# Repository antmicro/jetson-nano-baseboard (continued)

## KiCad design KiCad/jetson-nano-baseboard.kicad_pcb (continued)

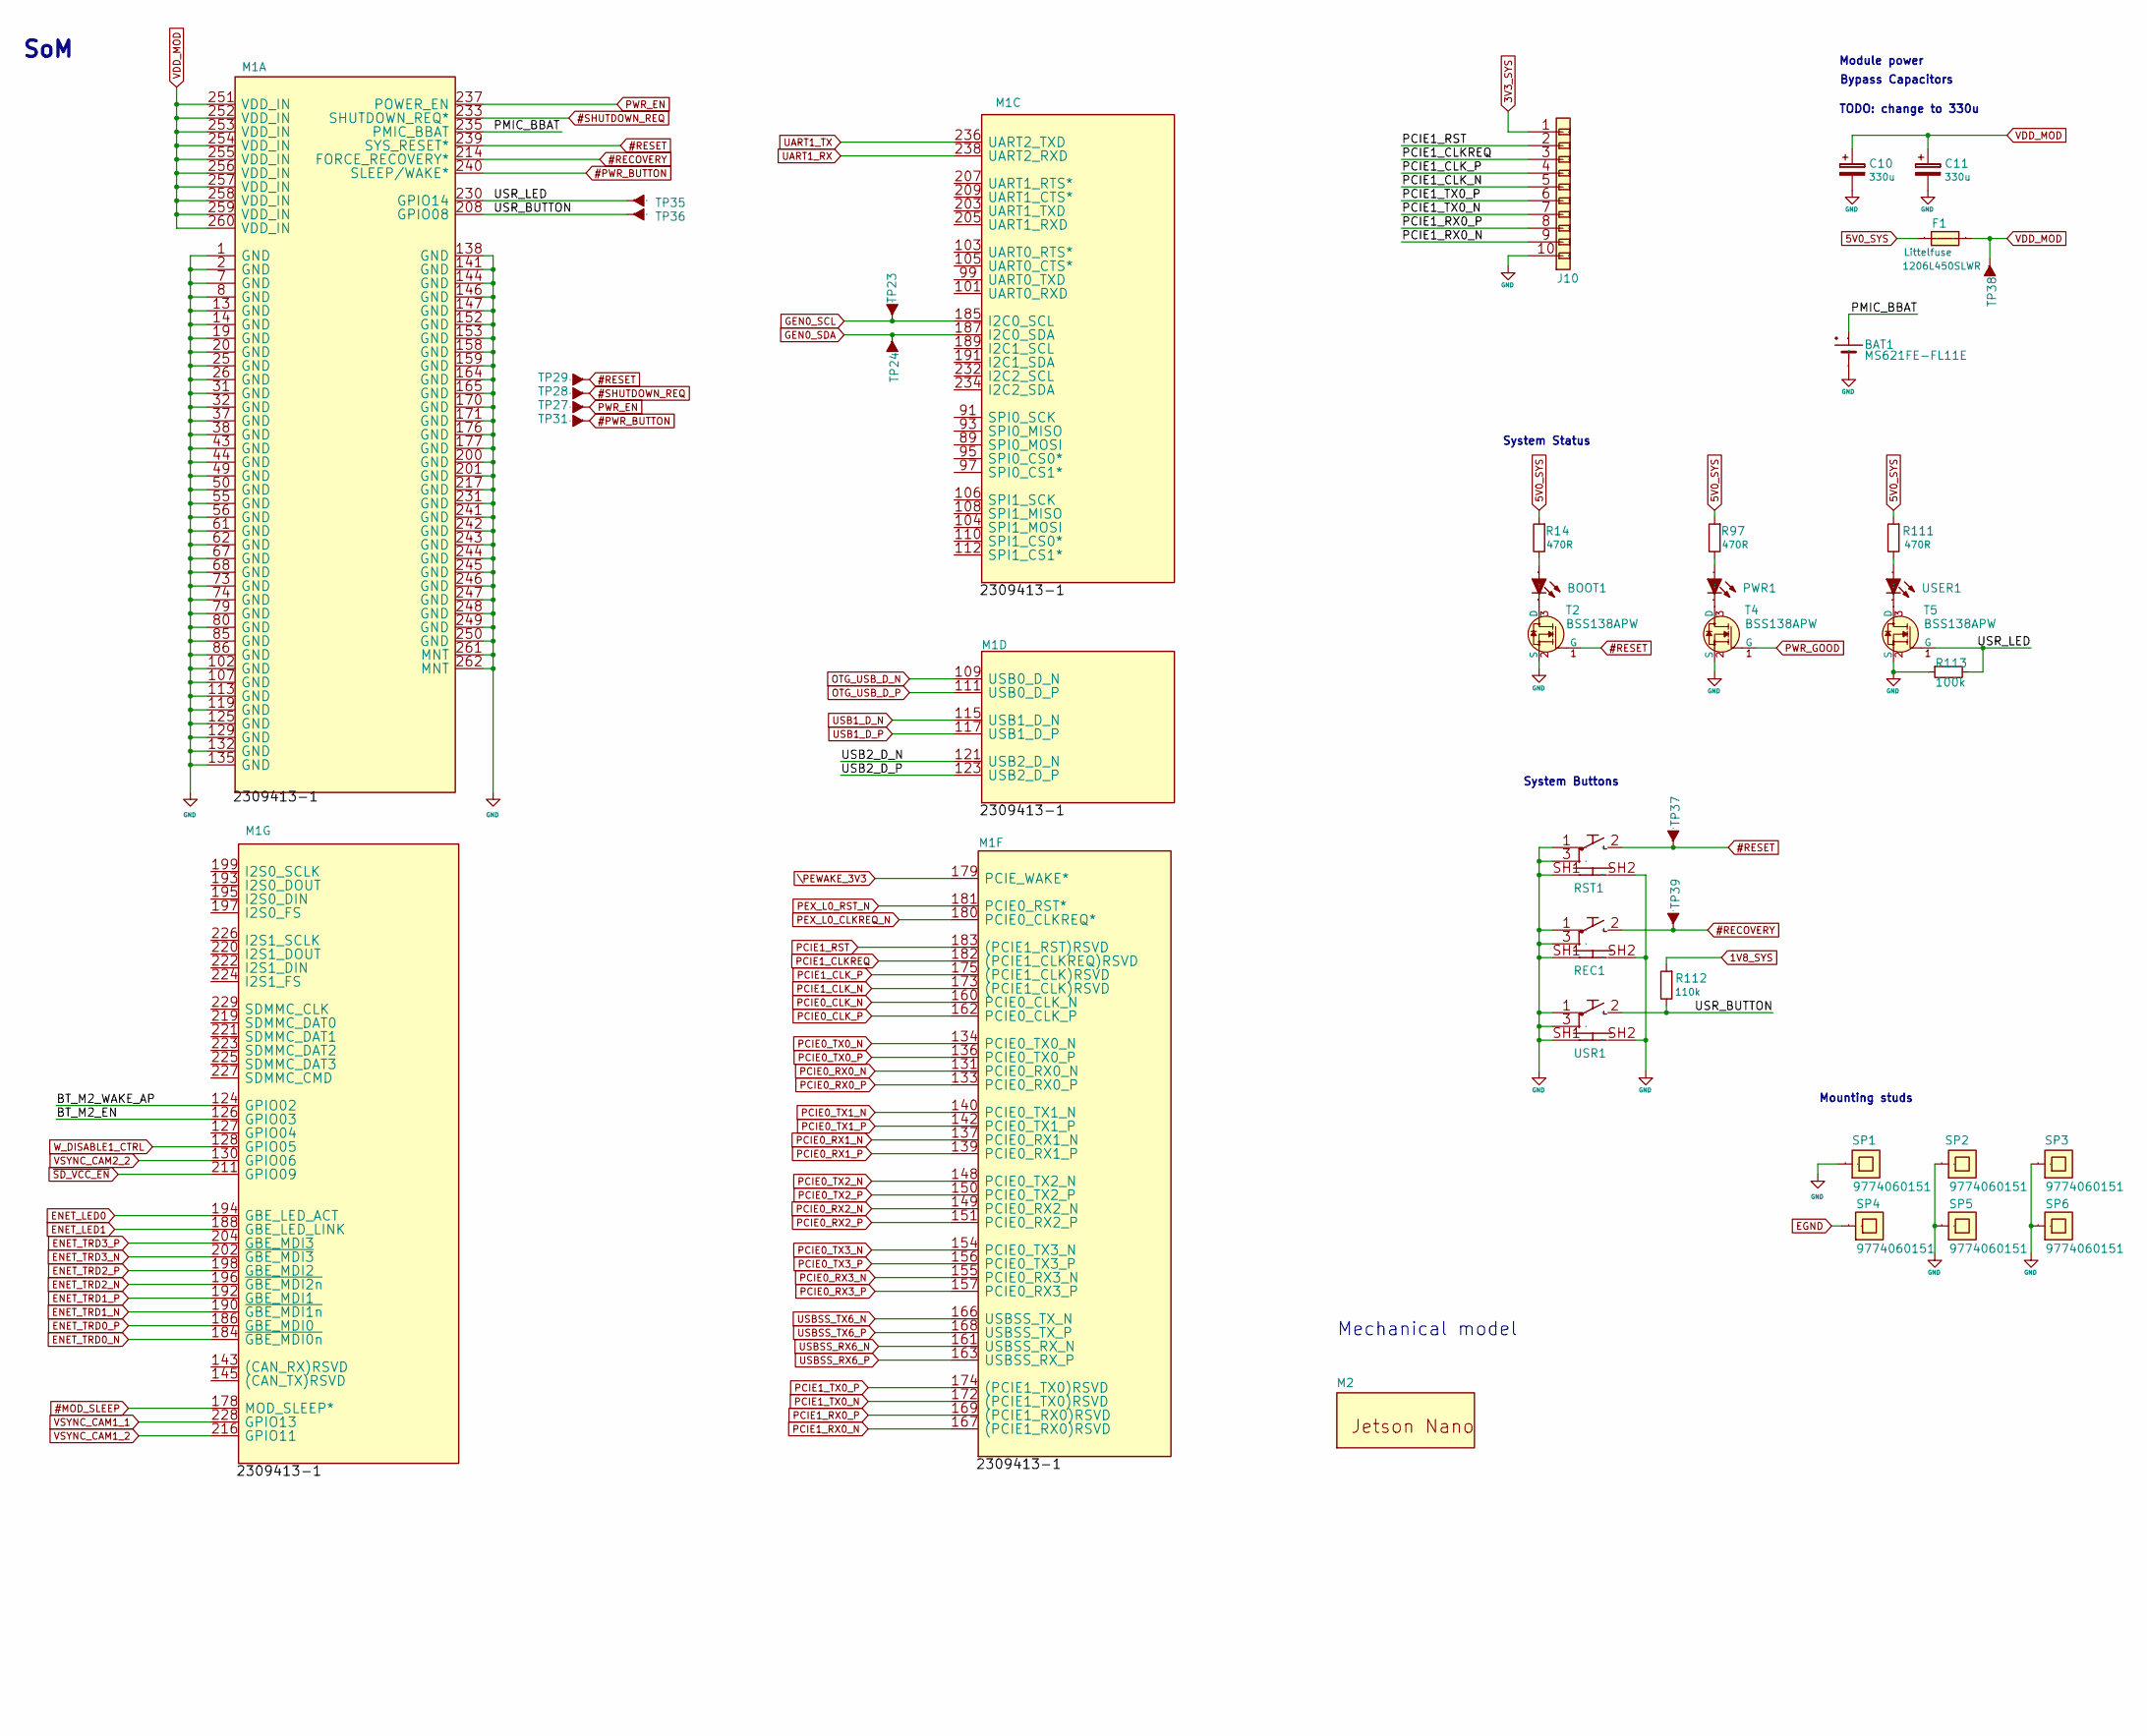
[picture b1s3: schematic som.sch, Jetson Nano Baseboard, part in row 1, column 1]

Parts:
BAT1: MS621FE-FL11E; MPN MS621FE-FL11E
BOOT1: LED0603; MPN KPT-1608SGC
C10, C11: C_330u_KEMET_B; KEMET_B; MPN T520B337M006ATE040
F1: Fuse-1206; PartSymbol 1206L450SLWR
J10: PCA-10; MPN PCA-10
M1, M1_4: jetson-nano-connector; PartSymbol 2309413-1
M2: jetson-nano-module; MPN 900-13448-0020-000
PWR1: LED0603; MPN KPT-1608SGC
R14, R97, R111: R_470R_0402; 0402-res; MPN CRCW0402470RFKED
R112: R_110k_0603; 0603-res; MPN CPF0603B110KE1
R113: 100k; 0402; MPN ERJ2GE0R00X
REC1: TL3340AF160QG; PartSymbol TL3340AF160QG
RST1: TL3340AF160QG; PartSymbol TL3340AF160QG
SP1, SP2, SP3, SP4, SP5, SP6: 9774060151; M2.5-6mm; MPN 9774060151
T2, T4, T5: BSS138APW; SC70-3; MPN BSS138PW
TP23, TP24, TP27, TP28, TP29, TP31, TP35, TP36, TP37, TP38, TP39: TP-R-1.5; MPN N/A
USER1: LED0603; MPN KPT-1608SGC
USR1: TL3340AF160QG; PartSymbol TL3340AF160QG

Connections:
1V8_SYS: R112.2; also elsewhere on the board
3V3_SYS: J10.1; also elsewhere on the board
5V0_SYS: F1.1, R14.2, R97.2, R111.2; also elsewhere on the board
#MOD_SLEEP: M1.178 (MOD_SLEEP*); also elsewhere on the board
#PWR_BUTTON: M1.240 (SLEEP/WAKE*), TP31.1
#RECOVERY: M1.214 (FORCE_RECOVERY*), REC1.2, TP39.1
#RESET: M1.239 (SYS_RESET*), RST1.2, T2.1 (G), TP29.1, TP37.1; also elsewhere on the board
#SHUTDOWN_REQ: M1.233 (SHUTDOWN_REQ*), TP28.1; also elsewhere on the board
/SoM/BT_M2_EN: M1.126 (GPIO03)
/SoM/BT_M2_WAKE_AP: M1.124 (GPIO02)
/SoM/PMIC_BBAT: BAT1.+, M1.235 (PMIC_BBAT)
/SoM/USB2_D_N: M1.121 (USB2_D_N)
/SoM/USB2_D_P: M1.123 (USB2_D_P)
/SoM/USR_BUTTON: M1.208 (GPIO08), R112.1, TP36.1, USR1.2
/SoM/USR_LED: M1.230 (GPIO14), R113.1, T5.1 (G), TP35.1
EGND: SP4.1; also elsewhere on the board
ENET_LED0: M1.194 (GBE_LED_ACT); also elsewhere on the board
ENET_LED1: M1.188 (GBE_LED_LINK); also elsewhere on the board
ENET_TRD0_N: M1.184 (~GBE_MDI0n); also elsewhere on the board
ENET_TRD0_P: M1.186 (GBE_MDI0); also elsewhere on the board
ENET_TRD1_N: M1.190 (~GBE_MDI1n); also elsewhere on the board
ENET_TRD1_P: M1.192 (GBE_MDI1); also elsewhere on the board
ENET_TRD2_N: M1.196 (~GBE_MDI2n); also elsewhere on the board
ENET_TRD2_P: M1.198 (GBE_MDI2); also elsewhere on the board
ENET_TRD3_N: M1.202 (~GBE_MDI3); also elsewhere on the board
ENET_TRD3_P: M1.204 (GBE_MDI3); also elsewhere on the board
GEN0_SCL: M1.185 (I2C0_SCL), TP23.1; also elsewhere on the board
GEN0_SDA: M1.187 (I2C0_SDA), TP24.1; also elsewhere on the board
unnamed: BOOT1.A, R14.1
unnamed: BOOT1.K, T2.3 (D)
unnamed: PWR1.A, R97.1
unnamed: PWR1.K, T4.3 (D)
unnamed: R111.1, USER1.A
unnamed: T5.3 (D), USER1.K
OTG_USB_D_N: M1.109 (USB0_D_N); also elsewhere on the board
OTG_USB_D_P: M1.111 (USB0_D_P); also elsewhere on the board
PCIE0_CLK_N: M1.160 (PCIE0_CLK_N); also elsewhere on the board
PCIE0_CLK_P: M1.162 (PCIE0_CLK_P); also elsewhere on the board
PCIE0_RX0_N: M1.131 (PCIE0_RX0_N); also elsewhere on the board
PCIE0_RX0_P: M1.133 (PCIE0_RX0_P); also elsewhere on the board
PCIE0_RX1_N: M1.137 (PCIE0_RX1_N); also elsewhere on the board
PCIE0_RX1_P: M1.139 (PCIE0_RX1_P); also elsewhere on the board
PCIE0_RX2_N: M1.149 (PCIE0_RX2_N); also elsewhere on the board
PCIE0_RX2_P: M1.151 (PCIE0_RX2_P); also elsewhere on the board
PCIE0_RX3_N: M1.155 (PCIE0_RX3_N); also elsewhere on the board
PCIE0_RX3_P: M1.157 (PCIE0_RX3_P); also elsewhere on the board
PCIE0_TX0_N: M1.134 (PCIE0_TX0_N); also elsewhere on the board
PCIE0_TX0_P: M1.136 (PCIE0_TX0_P); also elsewhere on the board
PCIE0_TX1_N: M1.140 (PCIE0_TX1_N); also elsewhere on the board
PCIE0_TX1_P: M1.142 (PCIE0_TX1_P); also elsewhere on the board
PCIE0_TX2_N: M1.148 (PCIE0_TX2_N); also elsewhere on the board
PCIE0_TX2_P: M1.150 (PCIE0_TX2_P); also elsewhere on the board
PCIE0_TX3_N: M1.154 (PCIE0_TX3_N); also elsewhere on the board
PCIE0_TX3_P: M1.156 (PCIE0_TX3_P); also elsewhere on the board
PCIE1_CLKREQ: J10.3, M1.182 ((PCIE1_CLKREQ)RSVD)
PCIE1_CLK_N: J10.5, M1.173 ((PCIE1_CLK)RSVD)
PCIE1_CLK_P: J10.4, M1.175 ((PCIE1_CLK)RSVD)
PCIE1_RST: J10.2, M1.183 ((PCIE1_RST)RSVD)
PCIE1_RX0_N: J10.9, M1.167 ((PCIE1_RX0)RSVD)
PCIE1_RX0_P: J10.8, M1.169 ((PCIE1_RX0)RSVD)
PCIE1_TX0_N: J10.7, M1.172 ((PCIE1_TX0)RSVD)
PCIE1_TX0_P: J10.6, M1.174 ((PCIE1_TX0)RSVD)
PEX_L0_CLKREQ_N: M1.180 (PCIE0_CLKREQ*); also elsewhere on the board
PEX_L0_RST_N: M1.181 (PCIE0_RST*); also elsewhere on the board
PWR_EN: M1.237 (POWER_EN), TP27.1; also elsewhere on the board
PWR_GOOD: T4.1 (G); also elsewhere on the board
UART1_RX: M1.238 (UART2_RXD); also elsewhere on the board
UART1_TX: M1.236 (UART2_TXD); also elsewhere on the board
USB1_D_N: M1.115 (USB1_D_N); also elsewhere on the board
USB1_D_P: M1.117 (USB1_D_P); also elsewhere on the board
USBSS_RX6_N: M1.161 (USBSS_RX_N); also elsewhere on the board
USBSS_RX6_P: M1.163 (USBSS_RX_P); also elsewhere on the board
USBSS_TX6_N: M1.166 (USBSS_TX_N); also elsewhere on the board
USBSS_TX6_P: M1.168 (USBSS_TX_P); also elsewhere on the board
VDD_MOD: C10.1, C11.1, F1.2, M1.251 (VDD_IN), M1.252 (VDD_IN), M1.253 (VDD_IN), M1.254 (VDD_IN), M1.255 (VDD_IN), M1.256 (VDD_IN), M1.257 (VDD_IN), M1.258 (VDD_IN), M1.259 (VDD_IN), M1.260 (VDD_IN), TP38.1
VSYNC_CAM1_1: M1.228 (GPIO13); also elsewhere on the board
VSYNC_CAM1_2: M1.216 (GPIO11); also elsewhere on the board
VSYNC_CAM2_2: M1.130 (GPIO06); also elsewhere on the board
W_DISABLE1_CTRL: M1.128 (GPIO05)
\PEWAKE_3V3: M1.179 (PCIE_WAKE*); also elsewhere on the board
~SD_VCC_EN~: M1.211 (GPIO09)

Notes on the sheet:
Mechanical model
Mounting studs
Bypass Capacitors
System Buttons
System Status
Module power
Text
SoM
TODO: change to 330u

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
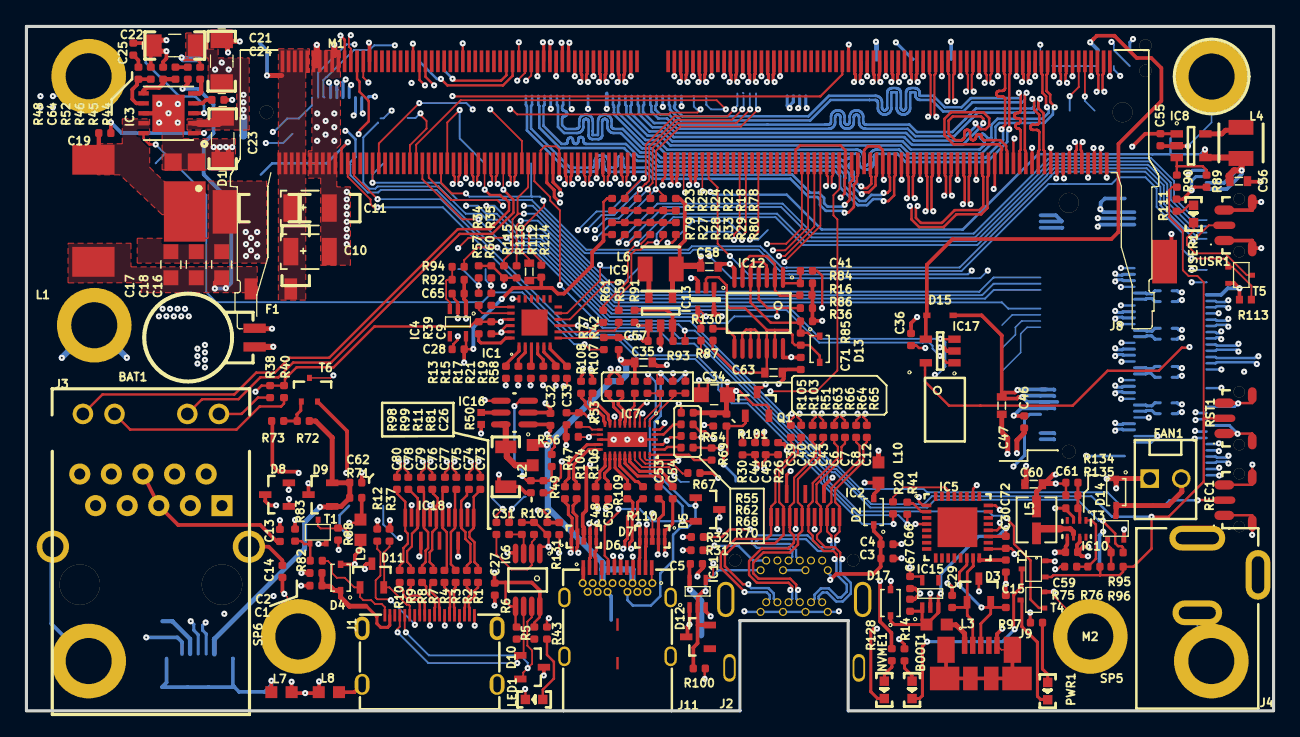
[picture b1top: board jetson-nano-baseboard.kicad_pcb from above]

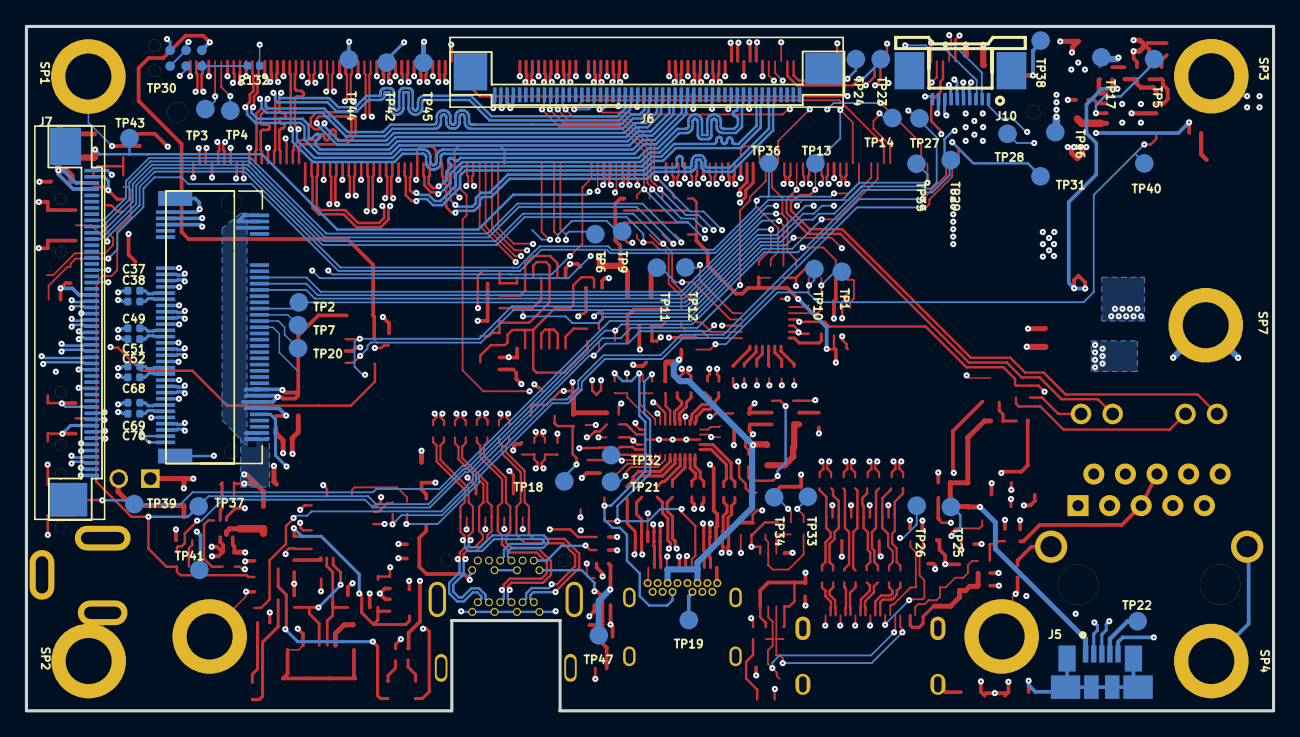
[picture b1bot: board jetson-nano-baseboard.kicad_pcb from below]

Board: 8 copper layers, 100.2 x 55.0 mm, 325 parts (63 on the bottom side), 312 nets.

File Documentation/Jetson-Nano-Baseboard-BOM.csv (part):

Designator,Value,Description,Quantity,PartNumber,Manufacturer,PartSymbol

"BOOT, LED1, PWR","KPT-1608SGC","LED Green 0603 case","3","LED_G","KINGBRIGHT","KPT-1608SGC"
"C1, C2, C3, C4","4u7","MLCC SMT Capacitor 4.7uF 0402","4","C_4u7_0402","MURATA","GRM155R60G475ME"
"C5, C19, C26, C27, C30, C33","100n","MLCC SMT Capacitor 100nF 0603","6","C_100n_0603","AVX","0603YC104KAZ2A"
"C6, C7, C8, C9, C12, C39, C40, C42, C43, C44, C45, C48, C50, C53, C54, C73, C74, C75, C76, C77, C78, C79, C80","100n","MLCC SMT Capacitor 100n 0402","23","C_100n_0402","TDK","C1005X5R0J104K050BA"
"C10, C11","100u","MLCC SMT Capacitor 100uF 1206","2","C_100u_1206","VISHAY","TMCMA0J107MTRF"
"C13","10n","MLCC SMT Capacitor 10 nF 0603","1","C_10n_0603","AVX","06031C103JAT2A"
"C14","100p","MLCC SMT Capacitor 100pF 0603","1","C_100p_0603","Walsin","0603N101J500CT"
"C15, C29","47p","MLCC SMT Capacitor 47pF 0603","2","C_47p_0603","AVX","06031A470KAT2A"
"C16, C17, C18, C34","47u","MLCC SMT Capacitor 47uF 0805","4","C_47u_0805","KEMET","C0805C476M9PACTU"
"C21, C22, C23","2u2","MLCC SMT Capacitor 2.2uF 1206","3","C_2u2_1206","KEMET","C1206C225J5RACTU"
"C24, C61","10n","MLCC SMT Capacitor 10 nF 0402","2","C_10n_0402","AVX","04025G103ZAT2A"
"C25","4n7","MLCC SMT Capacitor 4.7 nF 0402","1","C_4n7_0402","TDK","CGA2B3X7S2A472K050BB"
"C28, C63, C66","1u","MLCC SMT Capacitor 1uF 0402","3","C_1u_0402","MULTICOMP","MC0402F105Z6R3CT"
"C31","100u","MLCC SMT Capacitor 100uF 1210","1","C_100u_1210","SAMSUNG","CL32A107MQVNNNE"
"C32, C59","1u","MLCC SMT Capacitor 1uF 0603","2","C_1u_0603","KEMET","C0603C105M4PACTU"
"C35, C56, C58","10u","MLCC SMT Capacitor 10uF 0603","3","C_10u_0603","Walsin","0603X106M6R3CT"
"C41","47n","MLCC SMT Capacitor 47nF 0402","1","C_47n_0402","MULTICOMP","MC0402X473K160CT"
"C55, C57, C62","4u7","MLCC SMT Capacitor 4.7uF 0603","3","C_4u7_0603","MULTICOMP","MC0603X475K6R3CT"
"C60","10u","MLCC SMT Capacitor 10uF 0402","1","C_10u_0402","TDK","C1005X5R0J106M050BC"
"C64","47p","MLCC SMT Capacitor 47pF 0402","1","C_47p_0402","KEMET","C0402C470J5GACTU"
"C65, C67","2u2","MLCC SMT Capacitor 2.2uF 0402","2","C_2u2_0402","TDK","C1005X5R1A225K050BC"
"D1","PDS760-13","DIODE SCHOTTKY 60V 7A POWERDI5","1","PDS760-13","DIODES INC.","PDS760-13"
"D2, D4, D13, D14","1N4148WS","Diode small signal","4","1N4148WS","ON SEMICONDUCTOR","1N4148WS"
"D3, D5, D8, D9, D10, D11, D12","TPD2E009DRTR","ESD Suppressors 2-CH","7","TPD2E009DRTR","Texas Instruments","TPD2E009DRTR"
"D6, D7","TPD4E05U06","ESD Suppressors 4-CH","2","TPD4E05U06_PASS","Texas Instruments","TPD4E05U06DQAR"
"F1","1206L450SLWR","PTC RESET 6V LO RHO 1206 4.50A","1","LITTELFUSE_1206L450SLWR","LITTELFUSE","1206L450SLWR"
"FAN","MX-22-23-2021","Pinhead connector with key","1","molex_2223-2021","Molex","022232021 A-6373-02A222"
"IC1","TCA9548ARGER","TCA9548ARGER  I2C SWITCH W/ RESET, 8-CH, VQFN-24","1","TCA9548ARGER","Texas Instruments","TCA9548ARGER"
"IC2, IC18","TPD8S009","8-Channel ESD Protection for DisplayPort and HDMI","2","TPD8S009","Texas Instruments","TPD8S009DSMR"
"IC3","TPS54561-Q1","IC REG BCK SPLIT RAIL ADJ 10WSON","1","TPS54561-Q1","Texas Instruments","TPS54561-Q1"
"IC4, IC15","TLV70018DCKT","Voltage Regulator, 2V to 5.5V, 175mV Dropout, 1.8Vout, 200mAout","2","TLV70018DCKT","Texas Instruments","TLV70018DCKT"
"IC5","FT232RQ","USB to serial UART interface","1","FT232RQ","FTDI","FT232RQ-REEL"
"IC6","PCA9517ATP","I2C BUS REPEATER W/ LEVEL TRANS, HWSON-8","1","PCA9517ATP","NXP","PCA9517ATP"
"IC7","HD3SS3220","IC DRP PORT CTLR USB-C 30WQFN","1","HD3SS3220","Texas Instruments","HD3SS3220RNHT"
"IC8, IC9","LM3671MF-3.3","DC/DC Buck Converter","2","LM3671MF-3.3","Texas Instruments","LM3671MF-3.3/NOPB"
"IC10","LP2985-33DBVR","Fixed LDO Voltage Regulator, 2.2V to 16V, 280mV Dropout, 3.3Vout, 150mAout, SOT-23-5","1","LP2985-33DBVR","Texas Instruments","LP2985-33DBVR"
"IC11","SN74LV1T125DCKR","Buffer, 74LV1T125, 1.6 V to 5.5 V, SOT-23-5","1","SN74LV1T125DCKR","Texas Instruments","SN74LV1T125DCKR"
"IC12","74HC00BQ","2 NAND Gate, 4 channel","1","74HC00BQ","NEXPERIA","74HC00BQ"
"IC13","SN74LVC1G126DCKR","Buffer, tri-state","1","SN74LVC1G126DCKR","Texas Instruments","SN74LVC1G126DCKR"
"IC14","SN74LVC1G07DCKR","Buffer, open drain","1","SN74LVC1G07DCKR","Texas Instruments","SN74LVC1G07GW"
"IC16","NCP380HSNAJAAT1G","POWER LOAD SWITCH, HIGH SIDE","1","NCP380HSNAJAAT1G","ON SEMICONDUCTOR","NCP380HSNAJAAT1G"
"J1","685119136923","CONN HDMI FEMALE R/A 19POS 2.6MM","1","WE_685119136923","WURTH ELEKTRONIK","WE_685119136923"
"J2","2129320-3","Mini Displayport Reverse Offset","1","2129320-3","TE Connectivity","2129320-3"
"J3","WE_7499110124","LAN-Transformer WE-RJ45LAN 10/100/1000 BaseT","1","WE_7499110124","WURTH ELEKTRONIK","7499110124"
"J4","MJ-179PH","DC Power Connector, Jack, 4 A, 1.95 mm, PCB Mount, Through Hole","1","DC_SOCKET","MULTICOMP","MJ-179PH"
"J5, J9","Molex 47346-0001","USB - micro B Receptacle Connector 5 Position Surface Mount, Right Angle, Horizontal","2","CON-Molex-47346-0001","Molex","473460001"
"J6, J7","68715014522","0.50mm SMT ZIF Horizontal Bottom Contact WR-FPC","2","WE-687-150-145-22","WURTH ELEKTRONIK","68715014522"
"J11","632723300011","USB 3.1 Type C Receptacle Horizontal THR WR-COM","1","WE_632723300011","WURTH ELEKTRONIK","632723300011"
"L1","WE_7447798720","Fixed Inductors WE-PDF 1064 7.2uH 7.9A 12.8mOhm","1","WE_7447798720","WURTH ELEKTRONIK","7447798720"
"L2","BLM18EG221SN1D","MURATA  BLM18EG221SN1D  FERRITE BEAD, 0.05OHM, 2A, 0603","1","BLM18EG221SN1D","MURATA","BLM18EG221SN1D"
"L3","742792022","MURATA  BLM18EG221SN1D  FERRITE BEAD, 0.05OHM, 2A, 0603","1","742792022","WURTH ELEKTRONIK","742792022"
"L4, L6","LQH3NPN2R2NM0L","INDUCTOR, 2.2 ?H, ? 30%, 1212, 90 MHz, 0.073 ohm","2","LQH3NPN2R2NM0L","MURATA","LQH3NPN2R2NM0L"
"L7, L8, L9, L10","BLM18SG121TN1D","FERRITE BEAD, 0.025OHM, 3A, 0603","4","BLM18SG121TN1D","MURATA","BLM18SG121TN1D"
"M1","2309413-1","Memory Socket, DDR4, SODIMM Socket, 260 Contacts, Copper Alloy, Gold Plated Contacts","1","2309413-1","TE Connectivity","2309413-1"
"M2","","","1","jetson-nano-module","",""
"Q1","PMV32UP","P CH, 20V, 4A","1","PMV32UP","NXP","PMV32UP"
"Q2","PMV16XN","MOSFET, N CH","1","PMV16XN","NXP","PMV16XN"
"R1, R2, R3, R4, R7, R8, R9, R10","5R6","RES, 5R6, 0402","8","R_5R6_0402","Panasonic","ERJ2GEJ5R6X"
"R5, R6, R11, R88","10k","RES, 10k, 0603","4","R_10k_0603","BOURNS","CR0603-JW-103ELF"
"R12, R13, R15, R17, R19, R21, R39, R49, R57, R58, R59, R60, R61, R62, R63, R65, R68, R71, R76, R78, R80, R82, R90, R92, R93, R94, R98, R99, R103, R104, R105, R106, R107, R108, R109, R110","0R","RES, 0R, 0402","36","R_0R_0402","Panasonic","ERJ2GE0R00X"
"R14, R97","470R","RES, 470R, 0402","2","R_470R_0402","VISHAY","CRCW0402470RFKED."
"R16, R36, R96","1k","RES, 1k, 0402","3","R_1k_0402","BOURNS","CR0402-FX-1001GLF"
"R18, R22, R24, R25, R27, R28, R29, R33, R34, R35","2k","RES, 2k, 0402","10","R_2k_0402","VISHAY","CRCW04022K00FKED"
"R20, R41","22R","RES, 22R, 0402","2","R_22R_0402","VISHAY","CRCW040222R0FKED"
"R26, R30, R100, R101","100k","RES, 100k, 0603","4","R_100k_0603","BOURNS","CR0603-FX-1003HLF"
"R31, R32","1M","RES, 1M, 0603","2","R_1M_0603","BOURNS","CR0603-JW-105GLF"
"R38, R40","220R","RES, 220R, 0402","2","R_220R_0402","TE Connectivity","CRG0402J220R"
"R43","10k2","RES, 470R, 0603","1","R_470R_0603","BOURNS","CR0603-JW-471GLF"
"R44","243k","RES, 243k, 0402","1","R_243k_0402","MULTICOMP","MCMR04X2433FTL"
"R45","49R9","RES, 49R9, 0402","1","R_49R9_0402","VISHAY","CRCW040249R9FKED"
"R46","53k6","RES, 53k6, 0402","1","R_53k6_0402","TE Connectivity","CPF0402B53K6E1"
"R48","16k9","RES, 16k9, 0402","1","R_16k9_0402","Panasonic","ERA2AEB1692X"
"R50","10k2","RES, 5k6, 0603","1","R_5k6_0603","Panasonic","ERJ3GEYJ562V"
"R51","909k","RES, 909k, 0402","1","R_909k_0402","Panasonic","ERJ2RKF9093X"
"R52","10k2","RES, 10k2, 0402, 0.1%","1","R_10k2_0402_0.1%","TE Connectivity","CPF0402B10K2E1"
"R53, R67, R84","200k","RES, 200k, 0402","3","R_200k_0402","YAGEO","RC0402FR-07200KL"
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
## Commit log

2019-03-18 Initial commit.
2019-03-18 Added README.
2019-03-19 Change letter to lowercase
2019-04-12 doc: fix typos
2019-04-17 Updated pads for Displayport connector Corrected I2C connection for camera interface Added Q1 that inverts control logic that drives EN pin of IC16 Added pull-down R100 that controls Hotplug signal f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
2019-05-27 Clarify name
2019-07-26 Standardize LICENSE to be auto-recognized by GitHub
2019-09-17 Update schematic symbol for Nano
2019-09-17 Update schematics with new pinout
2019-09-17 Update PCB layout
2019-09-17 Update PDF documentation
2020-02-23 Add rev. 1.3
2020-02-23 Update assembly guidelines
2020-02-23 Add layout information to README
2020-03-06 Add 3D models
2020-03-06 Add 3D STEP model
2020-03-06 Fix PrjPcb
2020-03-06 Update README to mention Xavier NX
2020-03-06 Resolve documentation discrepancy
2020-03-11 Update schematic stylesheet
2020-04-15 Clarify there are up to 4 MIPI CSI interfaces
2020-04-21 Remove OutJob from project file
2020-04-21 Add release 1.4.2
2020-04-24 Reference the fact that NX was released
2020-05-25 Fix links.
2020-05-28 Update copyright notice
2020-07-16 Add mention of license
2020-07-16 Use RST syntax
2020-07-16 Add link to model
2020-10-12 Add Revision 1.4.6
2020-10-12 Update link to mechanical model
2020-10-12 Add documentation for release 1.4.6
2020-10-12 Add mention about purchasing option
2020-11-12 Add revision 1.4.7
2020-12-02 README: Add mention about BSP
2021-01-14 README: update BSP section
2021-01-20 Update copyrights year
2021-01-29 Update LICENSE
2021-02-02 Update link to 3D model
2021-02-09 Minor updates to README
2021-03-03 Add kernel patches for AV cameras
2021-03-22 README: added higher resolution layout image
2021-06-04 Move the Altium design files to a separate directory
2021-06-04 Add KiCad counterpart for 1.4.7
2021-06-04 Add STEP models
2021-06-09 Fix R113 connection
2021-06-09 Update 3d models and clean up designators
2021-06-09 Fix DRC errors
2021-06-09 Add PCB stackup table
2021-06-09 Add logo and clean up libraries
2021-06-09 Clean up B.SilkS layer
2021-06-17 Add CRC logo
2021-06-24 Notes added by 'git notes add'
2021-06-24 Fix README formatting
2021-10-01 Added ferrite beads before DC/DC and SOM
2021-12-31 DCDC passives copied
2021-12-31 Change P3448 aka xavier module to virtual
2021-12-31 Update PCB with shematic changes
2021-12-31 Clean artifacts, clean space for a new DCDC
2021-12-31 Change HDMI connector on schematic
2021-12-31 Clean copied parts
2021-12-31 Change HDMI connector on PCB
2021-12-31 Grouping parts around DCDC
2021-12-31 Update default silk size
2021-12-31 Change fan design to match Nvidia. Change user button and led pins
2021-12-31 Update TPD2E009DBZR to PESD2USB5UV-TR on PCB
2021-12-31 Rotate D9 to fit connections
2021-12-31 Replace ethernet connector, fix traces and tuning
2021-12-31 Cleanup wire stubs and artifacts
2021-12-31 Move ethernet connector closet to the edge. Loclib
2021-12-31 Fix traces after moving ethernet
2021-12-31 Import DRC rules
2021-12-31 Change placement of the eeprom
2021-12-31 Change I2C mux
2021-12-31 Fix placement of some components, minor fsilk changes
2021-12-31 Moving thing around
2021-12-31 Layout 5V DCDC, check traces, fix ffab references size
2021-12-31 Move items to fit in borders
2021-12-31 Disconnect pin 3 and 12 of LM604x0. Based on layout from datasheet
2021-12-31 Replace 5V0 and 3V3 DCDC
2021-12-31 Changed DP connector to micro HDMI on schematic
2021-12-31 Minor placement fixes
2021-12-31 Add missing 3D model
2021-12-31 Fix symbols, change DCDCC output capacitors to 0805
2021-12-31 5V0 DCDC fitting
2021-12-31 Replace NCP380HS with AP22652W6-7
2021-12-31 Rework 3V3 and 5V DCDC on schematic, layout 3V3 DCDC
2021-12-31 Cache and lib-table update
2021-12-31 Update comments, move things around on PCB
2021-12-31 Changed package of SN74LV1T125 to SOT32
2021-12-31 Change TPD2E009DBZR with PESD2USB5UV-TR on schematic
2021-12-31 Move OSHW logo away from track
2021-12-31 Placement of DCDC and passives
2021-12-31 Add T7 to reverse logic, cleanup silks
2021-12-31 DCDC placement, wiring of HDMI
2021-12-31 Move silks back into PCB
2021-12-31 Update README for the 1.5.x release
2021-12-31 Bump the design release to 1.5.0
2021-12-31 Fix img patches
2021-12-31 README: fix path
2022-01-03 Change R50 to 12k4
2022-01-03 Update 3V3 passives, add OR resistor to feedback network
2022-01-03 Change IC15 to TPS7A0518, loclib
2022-01-03 Change U3 to SN74LXC1T45DBVR
2022-01-03 Loclib, update schematic 5Vof DCDC and 3V3DCDC for cameras
2022-01-03 Save current status
2022-01-03 Finish routing, cleanup silks
2022-01-04 Adjust for EC errors
2022-01-04 Add comment to Usr led and button
2022-01-04 Refill zones
2022-01-04 Fix errors from EC
2022-01-05 Fix spacing issue on diff pair
2022-01-05 Update MPN of U1 and U5 to LM3671MF-3.3/NOPB
2022-01-05 Change BLM18EG221SN1D to BLM18SG121TN1D on schematic and PCB
2022-01-05 Change XFL4015-122MEC XFL4020-222MEC
2022-01-07 Fix power zone with thermal reliefs, minor silks cleanup
2022-01-07 Improving silks
2022-01-14 EC order E1379096
2022-02-03 Update MPS for FB2 FB3
2022-02-03 Update libraries
2022-02-03 Mark testpads as virtual
2022-02-03 Fix footprint libraries
2022-02-03 Make CRC logo as virtual
2022-02-03 Mark TAG connector as virtual
2022-02-03 Tweak EDP lanes
2022-02-03 Resolve overlapping courtyards
2022-02-03 Update layout after couryard tunning, DRC-Clean
2022-02-03 Remove date, assign revision 1.5.1
2022-02-04 Tweak designators
2022-02-04 Remove stud
2022-02-04 Add pin-1 marking to CSI connectors
2022-02-04 Assign Rev. 1.5.1 on schematic sheets
2022-02-07 Tune HDMI
2022-02-07 Cleanup stubs on enet, tune enet
2022-02-07 Tune EDP
2022-02-07 Change J10 to 5051101097
2022-02-07 Fix annotation on J10
2022-02-22 Add LM3671MF-3.3/NOPB to library, change U1 and U5 library reference
2022-02-25 Fix ethernet connector CT and GND connections
2022-02-25 Fix connections between resistors and DCDCs
2022-02-25 Update local libraries
2022-02-25 Update sym-lib-table
2022-03-02 LICENSE: bump dates
2022-03-22 Add T7 pull-down
2022-03-22 Add i2c-mux reset pull-up
2022-03-30 README: small fix
2022-04-06 Replace AP22652AW6-7 with AP22653W6-7
2022-04-15 README: minor updates
2022-04-15 README: describe changes introduced in Rev.1.5.x
2022-04-15 Cleanup
2022-04-15 README: add link to the Altium branch, remove outline
2022-04-15 Add logtypes to schematic sheets
2022-04-15 Add PDF schematic for rev.1.5.1
2022-04-15 README: describe the remaining directories
2022-05-25 Add Badge
2022-05-25 Change photo
2022-11-29 Add 32.7.2 patch for TX2-NX for AV cameras
2022-11-30 Update 32.7.2 patches
2022-12-23 Minor README fix
2023-02-13 added patch file for Xavier NX on Jetpack 5.0.2, along with a patching guide to help with installation and customisation
2023-02-14 fixed incorrect port-index inside nvcsi device-tree entry for J6 left camera
2023-02-17 simplified configurations supplied in patch, user can customise if there are other required permutations
2023-02-17 minor tweaks to readme
2023-03-31 Added block diagram to README, converted README to .md
2023-04-12 README: update wording
2023-05-05 Replaced 742792022 ferrites with 74279220181 for higher current capability
2023-05-05 Modified USBC ID logic
2023-05-05 Added OR resistors to connect IC7 to I2C bus
2023-05-05 Added I2C connector
2023-05-05 Added possibility to reset I2C mux from SoM GPIO
2023-05-05 Added resistor between RBOOT and CBOOT on 3V3_SYS regulator for reduced EMI
2023-05-05 Added CAN interface
2023-05-05 Added USB OTG functionality
2023-05-05 Fixed schematic connection between USB OTG shield and L7
2023-05-05 Migrated to KiCAD 6
2023-05-05 Auto cleanup tracks and vias
2023-05-05 Clear DRC warnings
2023-05-05 Adjust via and pads to have min 0.125mm annular ring
2023-05-05 Unify reference designator size. Hide values
2023-05-05 Sync PCB with schematics, place I2C/CAN connectors and part of the passives
2023-05-05 Fix SIC477ED note
2023-05-05 Resolve TOOD on USB sheet
2023-05-05 Route I2C and CAN to external connectors
2023-05-05 Remove fp-info-cache
2023-05-05 Route OTG USB signals. Connection to SOM tbd
2023-05-05 Improve USB 3.x routing. Route as DIFF 85Ohm on the top layer
2023-05-05 Connect remaining items
2023-05-05 Improved input protection - added TVSes, reverse polarity protection and input fuse
2023-05-05 Improve ground plane under USB 3.x signals
2023-05-05 Remove kicad_prl file
2023-05-05 Ignore KiCad files
2023-05-05 Sync PCB with schematic. Remove copper from NPTH holes
2023-05-05 Connect OTG VBUS_DET and ID_DET signals to SOM
2023-05-05 Update VBUS_DET label
2023-05-05 Add labels to the LEDs and buttons
2023-05-05 Improve USB-C load switch ctrl circuit
2023-05-05 Add some todos
2023-05-05 Add PCB SHA string
2023-05-05 Fix DRC errors. 3 connection TBD
2023-05-05 Replace USB power switches with version without output discharge
2023-05-05 Update parts enumeration
2023-05-05 Continue placement, mix USB SS signals as HD3SS3220 allows for it
2023-05-05 Bumped revision to 1.6.1
2023-05-05 Fixed D1 and D9 footprints
2023-05-05 ADD U8 to the local library
2023-05-05 Add #RESET pull-down
2023-05-05 Moved C35 farther from THT pins
2023-05-05 Updated loclib and synced it with schematic
2023-05-05 Align designators
2023-05-05 Update SC70-3 footprint in the loclib
2023-05-05 Replace D5 and D10 with a copy of D12
2023-05-05 Fix USB-OTG backfeed issue #44022
2023-05-05 Update local footprints
2023-05-08 Route USB-C_ID signal around 3.3V plane
2023-07-05 Add OHP link
2023-10-13 Standardize components
2023-10-13 50276 Add OHP assets and schematic PDF
2024-04-11 [#56834] Fix components links
2024-04-12 [#57913] fix 2309413-1
2025-09-18 [#83358] Update KiCad project files
2025-09-18 [#83366] Update README
2025-09-18 [#83358] Run kmake dnp
2025-09-18 [#83358] Repair broken footprints after symbols update
2025-09-18 [#83366] Repair Tag connector shortage
2025-09-18 [#83366] Add user.9 and user.5 layer
2025-09-18 [#83366] Update 0402 resistor
2025-09-18 [#83366] Remove SoM and Tag Connect from vis
2025-09-18 [#83358] Run kmake globlib
2025-09-18 [#83358] Repair broken symbol after update
2025-09-18 [#83358] Add .ci.yml
2025-12-31 [#83366] README: minor updates
2025-12-31 [#83366] Remove asset files
2025-12-31 [#83366] README: Add physical dimensions
